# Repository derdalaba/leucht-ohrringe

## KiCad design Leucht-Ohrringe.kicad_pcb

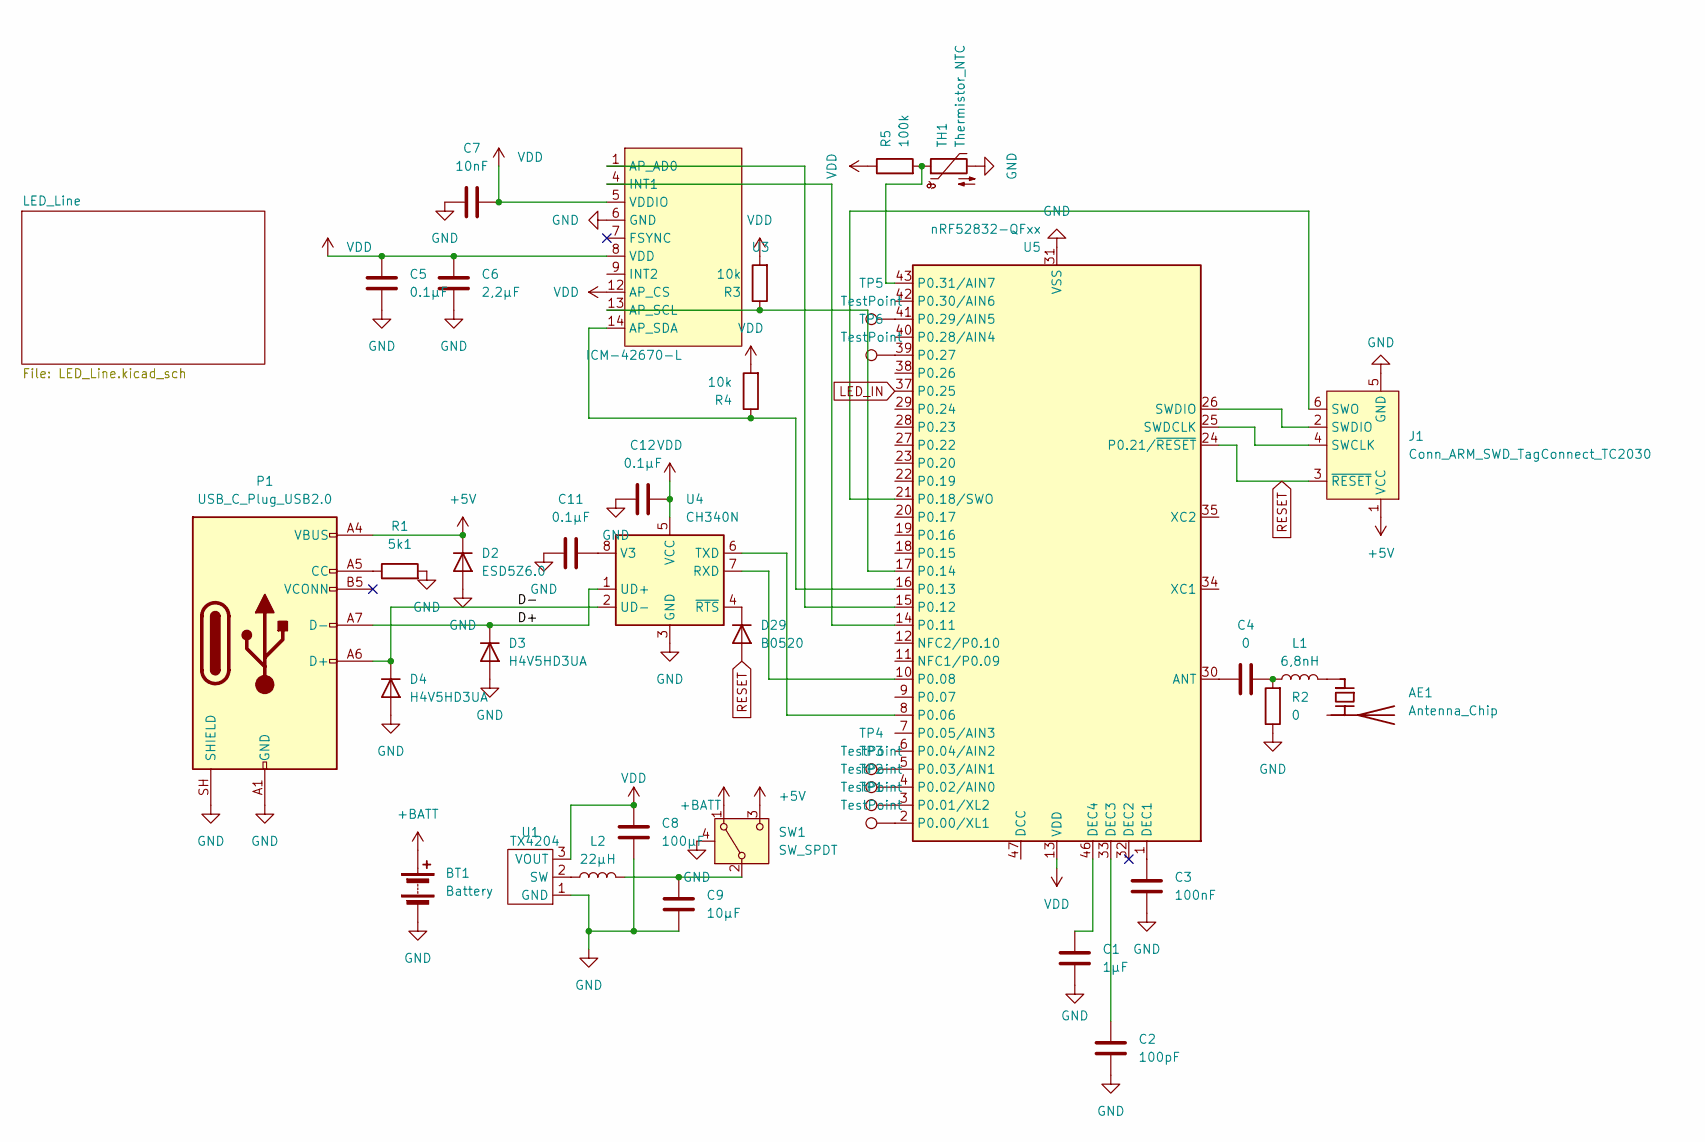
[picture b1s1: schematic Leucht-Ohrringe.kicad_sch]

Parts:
AE1: Antenna_Chip; RFANT3216120A5T; LCSC C127629
BT1: Battery; JST_SH_SM02B-SRSS-TB_1x02-1MP_P1.00mm_Horizontal
C1: 1µF; C_0402_1005Metric; LCSC C52923
C2: 100pF; C_0402_1005Metric; LCSC C1546
C3: 100nF; C_0402_1005Metric; LCSC C1525
C4: 0; C_0402_1005Metric; LCSC C17168
C5, C11, C12: 0.1µF; C_0402_1005Metric_Pad0.74x0.62mm_HandSolder; LCSC C1525
C6: 2,2µF; C_0402_1005Metric_Pad0.74x0.62mm_HandSolder; LCSC C12530
C7: 10nF; C_0402_1005Metric_Pad0.74x0.62mm_HandSolder; LCSC C15195
C8: 100µF; C_1206_3216Metric_Pad1.33x1.80mm_HandSolder; LCSC C15008
C9: 10µF; C_0603_1608Metric_Pad1.08x0.95mm_HandSolder; LCSC C19702
D2: ESD5Z6.0; D_SOD-523; LCSC C49437732
D3, D4: H4V5HD3UA; D_SOD-323; LCSC C54334010
D29: B0520; D_SOD-523; LCSC C2910120
J1: Conn_ARM_SWD_TagConnect_TC2030; Tag-Connect_TC2030-IDC-NL_2x03_P1.27mm_Vertical
L1: 6,8nH; L_0402_1005Metric; LCSC C77110
L2: 22µH; FNR3015S; LCSC C167761
P1: USB_C_Plug_USB2.0; USB_C_Receptacle_G-Switch_GT-USB-7010ASV; LCSC C668623
R1: 5k1; R_0603_1608Metric; LCSC C2907044
R2: 0; R_0402_1005Metric; LCSC C17168
R3, R4: 10k; R_0402_1005Metric_Pad0.72x0.64mm_HandSolder; LCSC C49247682
R5: 100k; R_0402_1005Metric_Pad0.72x0.64mm_HandSolder; LCSC C25741
SW1: SW_SPDT; K3-1236S
TH1: Thermistor_NTC; R_0402_1005Metric_Pad0.72x0.64mm_HandSolder; LCSC C49247682
TP1, TP2, TP3, TP4, TP5, TP6: TestPoint; TestPoint_0,5mm
U1: TX4204; SOT-23-3; LCSC C5122342
U3: ICM-42670-L; Bosch_LGA-14_3x2.5mm_P0.5mm; LCSC C49073546
U4: CH340N; JEITA_SOIC-8_3.9x4.9mm_P1.27mm; LCSC C2977777
U5: nRF52832-QFxx; QFN-48-1EP_6x6mm_P0.4mm_EP4.6x4.6mm

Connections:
+5V: D2.1 (K), J1.1 (VCC), P1.A4 (VBUS), P1.A9 (VBUS), P1.B4 (VBUS), P1.B9 (VBUS), SW1.3 (C)
+BATT: BT1.1 (+), SW1.1 (A); also elsewhere on the board
/D+: D3.1 (K), P1.A7 (D-), U4.1 (UD+)
/D-: D4.1 (K), P1.A6 (D+), U4.2 (UD-)
GND: BT1.2 (-), C1.2, C2.2, C3.2, C5.1, C6.2, C7.1, C8.2, C9.2, C11.2, C12.2, D2.2 (A), D3.2 (A), D4.2 (A), J1.5 (GND), P1.A1 (GND), P1.A12 (GND), P1.B1 (GND), P1.B12 (GND), P1.SH (SHIELD), R1.2, R2.1, SW1.4 (SHIELD), TH1.2, U1.1 (GND), U3.6 (GND), U4.3 (GND), U5.31 (VSS), U5.45 (VSS), U5.49 (VSS); also elsewhere on the board
LED_IN: U5.37 (P0.25); also elsewhere on the board
unnamed: AE1.1 (FEED_1), L1.2
unnamed: C4.2, L1.1, R2.2
unnamed: D29.1 (K), U4.4 (~RTS)
unnamed: J1.4 (SWCLK), U5.25 (SWDCLK)
unnamed: J1.2 (SWDIO), U5.26 (SWDIO)
unnamed: J1.6 (SWO), U5.21 (P0.18/SWO)
unnamed: P1.A5 (CC), R1.1
unnamed: C9.1, L2.2, SW1.2 (B)
unnamed: L2.1, U1.2 (SW)
unnamed: U3.1 (AP_AD0), U5.15 (P0.12)
unnamed: R3.1, U3.13 (AP_SCL), U5.17 (P0.14)
unnamed: R4.1, U3.14 (AP_SDA), U5.16 (P0.13)
unnamed: U3.4 (INT1), U5.14 (P0.11)
unnamed: U4.7 (RXD), U5.10 (P0.08)
unnamed: U4.6 (TXD), U5.8 (P0.06)
unnamed: C11.1, U4.8 (V3)
unnamed: C4.1, U5.30 (ANT)
unnamed: C3.1, U5.1 (DEC1)
unnamed: C2.1, U5.33 (DEC3)
unnamed: C1.1, U5.46 (DEC4)
unnamed: TP1.1 (1_1), U5.2 (P0.00/XL1)
unnamed: TP2.1 (1_1), U5.3 (P0.01/XL2)
unnamed: TP3.1 (1_1), U5.4 (P0.02/AIN0)
unnamed: TP4.1 (1_1), U5.5 (P0.03/AIN1)
unnamed: TP6.1 (1_1), U5.39 (P0.27)
unnamed: TP5.1 (1_1), U5.41 (P0.29/AIN5)
unnamed: R5.2, TH1.1, U5.43 (P0.31/AIN7)
RESET: D29.2 (A), J1.3 (~RESET), U5.24 (P0.21/~RESET)
VDD: C5.2, C6.1, C7.2, C8.1, C12.1, R3.2, R4.2, R5.1, U1.3 (VOUT), U3.5 (VDDIO), U3.8 (VDD), U3.12 (AP_CS), U4.5 (VCC), U5.13 (VDD), U5.36 (VDD), U5.48 (VDD)

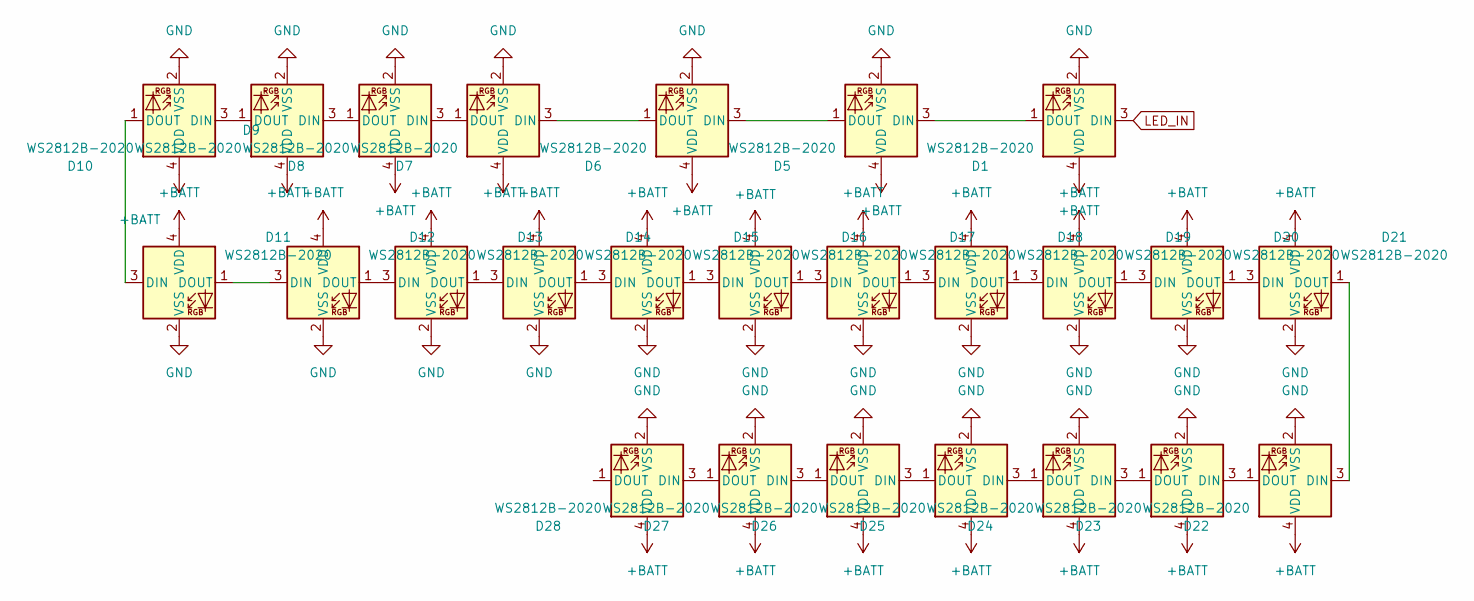
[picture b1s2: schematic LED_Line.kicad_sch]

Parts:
D1, D5, D6, D7, D8, D9, D10, D11, D12, D13, D14, D15, D16, D17, D18, D19, D20, D21, D22, D23, D24, D25, D26, D27, D28: WS2812B-2020; LED_WS2812B-2020_PLCC4_2.0x2.0mm

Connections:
+BATT: D1.4 (VDD), D5.4 (VDD), D6.4 (VDD), D7.4 (VDD), D8.4 (VDD), D9.4 (VDD), D10.4 (VDD), D11.4 (VDD), D12.4 (VDD), D13.4 (VDD), D14.4 (VDD), D15.4 (VDD), D16.4 (VDD), D17.4 (VDD), D18.4 (VDD), D19.4 (VDD), D20.4 (VDD), D21.4 (VDD), D22.4 (VDD), D23.4 (VDD), D24.4 (VDD), D25.4 (VDD), D26.4 (VDD), D27.4 (VDD), D28.4 (VDD); also elsewhere on the board
GND: D1.2 (VSS), D5.2 (VSS), D6.2 (VSS), D7.2 (VSS), D8.2 (VSS), D9.2 (VSS), D10.2 (VSS), D11.2 (VSS), D12.2 (VSS), D13.2 (VSS), D14.2 (VSS), D15.2 (VSS), D16.2 (VSS), D17.2 (VSS), D18.2 (VSS), D19.2 (VSS), D20.2 (VSS), D21.2 (VSS), D22.2 (VSS), D23.2 (VSS), D24.2 (VSS), D25.2 (VSS), D26.2 (VSS), D27.2 (VSS), D28.2 (VSS); also elsewhere on the board
LED_IN: D1.3 (DIN); also elsewhere on the board
unnamed: D1.1 (DOUT), D5.3 (DIN)
unnamed: D5.1 (DOUT), D6.3 (DIN)
unnamed: D6.1 (DOUT), D7.3 (DIN)
unnamed: D7.1 (DOUT), D8.3 (DIN)
unnamed: D8.1 (DOUT), D9.3 (DIN)
unnamed: D9.1 (DOUT), D10.3 (DIN)
unnamed: D10.1 (DOUT), D11.3 (DIN)
unnamed: D11.1 (DOUT), D12.3 (DIN)
unnamed: D12.1 (DOUT), D13.3 (DIN)
unnamed: D13.1 (DOUT), D14.3 (DIN)
unnamed: D14.1 (DOUT), D15.3 (DIN)
unnamed: D15.1 (DOUT), D16.3 (DIN)
unnamed: D16.1 (DOUT), D17.3 (DIN)
unnamed: D17.1 (DOUT), D18.3 (DIN)
unnamed: D18.1 (DOUT), D19.3 (DIN)
unnamed: D19.1 (DOUT), D20.3 (DIN)
unnamed: D20.1 (DOUT), D21.3 (DIN)
unnamed: D21.1 (DOUT), D22.3 (DIN)
unnamed: D22.1 (DOUT), D23.3 (DIN)
unnamed: D23.1 (DOUT), D24.3 (DIN)
unnamed: D24.1 (DOUT), D25.3 (DIN)
unnamed: D25.1 (DOUT), D26.3 (DIN)
unnamed: D26.1 (DOUT), D27.3 (DIN)
unnamed: D27.1 (DOUT), D28.3 (DIN)

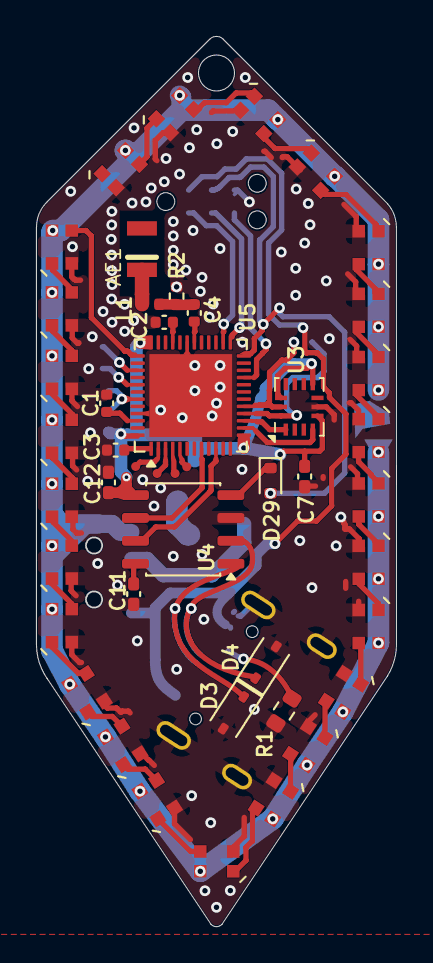
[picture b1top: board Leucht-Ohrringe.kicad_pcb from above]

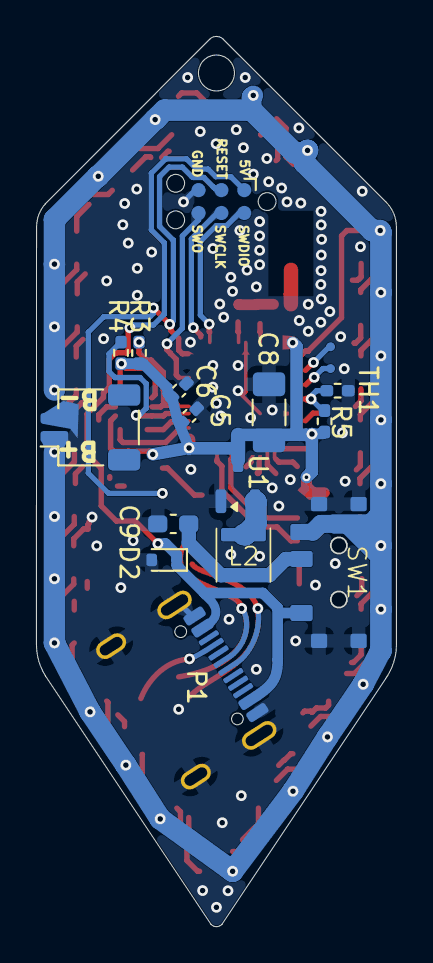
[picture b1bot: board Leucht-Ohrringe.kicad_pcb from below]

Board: 2 copper layers, 20.0 x 49.5 mm, 63 parts (17 on the bottom side), 59 nets.

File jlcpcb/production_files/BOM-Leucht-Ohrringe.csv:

Comment,Designator,Footprint,LCSC,Quantity
0,"C4,R2",C_0402_1005Metric,C17168,2
0.1µF,"C11,C12,C5",C_0402_1005Metric_Pad0.74x0.62mm_HandSolder,C1525,3
100k,R5,R_0402_1005Metric_Pad0.72x0.64mm_HandSolder,C25741,1
100nF,C3,C_0402_1005Metric,C1525,1
100pF,C2,C_0402_1005Metric,C1546,1
100µF,C8,C_1206_3216Metric_Pad1.33x1.80mm_HandSolder,C15008,1
10k,"R3,R4",R_0402_1005Metric_Pad0.72x0.64mm_HandSolder,C25744,2
10nF,C7,C_0402_1005Metric_Pad0.74x0.62mm_HandSolder,C15195,1
10µF,C9,C_0603_1608Metric_Pad1.08x0.95mm_HandSolder,C19702,1
1µF,C1,C_0402_1005Metric,C52923,1
"2,2µF",C6,C_0402_1005Metric_Pad0.74x0.62mm_HandSolder,C12530,1
22µH,L2,FNR3015S,C167761,1
5k1,R1,R_0603_1608Metric,C23186,1
"6,8nH",L1,L_0402_1005Metric,C77110,1
Antenna_Chip,AE1,RFANT3216120A5T,C127629,1
B0520,D29,D_SOD-523,C2910120,1
CH340N,U4,JEITA_SOIC-8_3.9x4.9mm_P1.27mm,C2977777,1
ESD5Z6.0,D2,D_SOD-523,C49437732,1
H4V5HD3UA,"D3,D4",D_SOD-323,C54334010,2
ICM-42670-L,U3,Bosch_LGA-14_3x2.5mm_P0.5mm,C49073546,1
TX4204,U1,SOT-23-3,C5122342,1
Thermistor_NTC,TH1,R_0402_1005Metric_Pad0.72x0.64mm_HandSolder,C49247682,1
USB_C_Plug_USB2.0,P1,USB_C_Receptacle_G-Switch_GT-USB-7010ASV,C668623,1
nRF52832-QFxx,U5,QFN-48-1EP_6x6mm_P0.4mm_EP4.6x4.6mm,C77540,1
WS2812B-2020,D23,LED_WS2812B-2020_PLCC4_2.0x2.0mm,,1
WS2812B-2020,D26,LED_WS2812B-2020_PLCC4_2.0x2.0mm,,1
WS2812B-2020,D20,LED_WS2812B-2020_PLCC4_2.0x2.0mm,,1
WS2812B-2020,D21,LED_WS2812B-2020_PLCC4_2.0x2.0mm,,1
WS2812B-2020,D18,LED_WS2812B-2020_PLCC4_2.0x2.0mm,,1
WS2812B-2020,D14,LED_WS2812B-2020_PLCC4_2.0x2.0mm,,1
WS2812B-2020,D25,LED_WS2812B-2020_PLCC4_2.0x2.0mm,,1
WS2812B-2020,D22,LED_WS2812B-2020_PLCC4_2.0x2.0mm,,1
WS2812B-2020,D19,LED_WS2812B-2020_PLCC4_2.0x2.0mm,,1
WS2812B-2020,D5,LED_WS2812B-2020_PLCC4_2.0x2.0mm,,1
WS2812B-2020,D11,LED_WS2812B-2020_PLCC4_2.0x2.0mm,,1
WS2812B-2020,D13,LED_WS2812B-2020_PLCC4_2.0x2.0mm,,1
WS2812B-2020,D24,LED_WS2812B-2020_PLCC4_2.0x2.0mm,,1
WS2812B-2020,D8,LED_WS2812B-2020_PLCC4_2.0x2.0mm,,1
WS2812B-2020,D10,LED_WS2812B-2020_PLCC4_2.0x2.0mm,,1
WS2812B-2020,D1,LED_WS2812B-2020_PLCC4_2.0x2.0mm,,1
WS2812B-2020,D6,LED_WS2812B-2020_PLCC4_2.0x2.0mm,,1
WS2812B-2020,D7,LED_WS2812B-2020_PLCC4_2.0x2.0mm,,1
WS2812B-2020,D16,LED_WS2812B-2020_PLCC4_2.0x2.0mm,,1
WS2812B-2020,D15,LED_WS2812B-2020_PLCC4_2.0x2.0mm,,1
WS2812B-2020,D17,LED_WS2812B-2020_PLCC4_2.0x2.0mm,,1
WS2812B-2020,D28,LED_WS2812B-2020_PLCC4_2.0x2.0mm,,1
WS2812B-2020,D27,LED_WS2812B-2020_PLCC4_2.0x2.0mm,,1
WS2812B-2020,D12,LED_WS2812B-2020_PLCC4_2.0x2.0mm,,1
WS2812B-2020,D9,LED_WS2812B-2020_PLCC4_2.0x2.0mm,,1
Battery,BT1,JST_SH_SM02B-SRSS-TB_1x02-1MP_P1.00mm_Horizontal,,1
TestPoint,TP2,"TestPoint_0,5mm",,1
TestPoint,TP3,"TestPoint_0,5mm",,1
TestPoint,TP4,"TestPoint_0,5mm",,1
TestPoint,TP1,"TestPoint_0,5mm",,1
SW_SPDT,SW1,K3-1236S,,1
TestPoint,TP6,"TestPoint_0,5mm",,1
TestPoint,TP5,"TestPoint_0,5mm",,1
